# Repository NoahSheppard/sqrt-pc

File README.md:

## **UNDER CONSTRUCTION**

# Sqrt(PC)
A mini PC helper with a battery, and a microcontroller powerful enough to run programs itself...

For now this repo will be kept simple, with just the bare essentials in it. If you want a more in-depth guide into my inner thought process and how things came together over time, and feel that the commit history is weak, please find the Blueprint link [here](https://blueprint.hackclub.com/projects/13283)

# Bill Of Materials
<!-- BOM_START -->
| Reference | Qty | Value | Footprint | Price ($AUD unless marked) | Purchase-URL | Label | Notes |
| --- | --- | --- | --- | --- | --- | --- | --- |
| C46 | 1 | 100nF | C315C104K5R5TA:CAPRR254W54L381T254H466B | $0.70 | https://au.mouser.com/ProductDetail/KEMET/C315C104K5R5TA?qs=AHmto%252BvZ7OG2Mx7li%2Fn8YQ%3D%3D | Power Circuit - 100nF Capacitor |  |
| D1 | D2 | D3 | D5 | D6 | D7 | 6 | ~ | ScottoKeebs_Components:Diode_DO-35 | $- | N/A | Diodes for the Keyswitch array |  |
| D4 | 1 | LED_ARBG | LED_SMD:LED_Kingbright_AAA3528ESGCT | $0.74 | https://au.mouser.com/ProductDetail/Kingbright/AAA3528ESGCT?qs=HXFqYaX1Q2ztii0bK20PQg%3D%3D | LED for battery status |  |
| D9 | D10 | D11 | D12 | D13 | D14 | 6 | LED_SK6812MINI | ScottoKeebs_Components:LED_SK6812MINI | $- | N/A | RGB LEDs |  |
| DS1 | 1 | 4311 | 4311:MODULE_4311 | $9.37 | https://www.aliexpress.com/item/1005009447193931.html | Screen |  |
| J1 | 1 | Conn_01x02 | Connector_Molex:Molex_PicoBlade_53048-0210_1x02_P1.25mm_Horizontal | $3.76 | https://www.aliexpress.com/item/32807183020.html | Battery Connector | Can only get 50 min |
| Q1 | 1 | AO3401A | Package_TO_SOT_SMD:SOT-23W_Handsoldering | $0.97 | https://www.aliexpress.com/item/1005008934110148.html | Power Circuit - P-Channel MOSFET - Power Latch | Can only get 10 min |
| R2 | 1 | FMP100JR-52-2K2 | KiCADv6:FMP100JR_52_2K2 | $0.19 | https://au.mouser.com/ProductDetail/YAGEO/FMP100JR-52-2K2?qs=wcZjbqjoJegNfVYDP1qQwg%3D%3D | Power Circuit - 2.2kOhm Resistor |  |
| R3 | R4 | 2 | MFR-25FBF52-1K | MFR-25FBF52-1K:RESAD1100W55L680D260 | $0.31 | https://au.mouser.com/ProductDetail/YAGEO/MFR-25FTF52-1K47?qs=gt1LBUVyoHl4e3xmkemLyA%3D%3D | Power Circuit - 1.47 kOhms Resistor |  |
| R5 | R6 | 2 | RNC55H1002FMRE7 | RNC55H1002FMRE7:RESAD1081W64L635D269 | $0.85 | https://www.jaycar.com.au/10k-ohm-0-5-watt-metal-film-resistors-pack-of-8/p/RR0596?srsltid=AfmBOooZybZRjXbsL3loWYFdbOO8xv4_Spoyh16NfgIc8Q6pRosaol9- | Power Circuit - 10kOhm Resistor | Can only get in a 8 pack for this cheap |
| RN1 | 1 | CAY16-1003F4LF | CAY16-1003F4LF:RESCAF80P320X160X60-8N | $0.15 | https://au.mouser.com/ProductDetail/Bourns/CAY16-1003F4LF?qs=T7l%2FPuJnbcT4dvX5HXX74Q%3D%3D&srsltid=AfmBOoqqP7U5jdrc4c8albsdljesYeuMQMlg74Kuni7se9EsMJJ111ZA | Power Circuit - 4 100kOhm Resistors |  |
| S1 | S2 | S3 | S5 | S6 | S7 | 6 | ~ | Button_Switch_Keyboard:SW_Cherry_MX_1.00u_PCB | $- | N/A | Keyswitches | I own these already |
| S8 | 1 | PTS526_SMG15_SMTR2_LFS | PTS526_SMG15_SMTR2_LFS:SW_PTS526_SMG15_SMTR2_LFS | $0.24 | https://au.mouser.com/ProductDetail/CK/PTS526SMG15SMTR2-LFS?qs=Imq1NPwxi76tu1Vo5JUXUg%3D%3D | Power Button |  |
| U1 | 1 | WEMOSC3mini | RF_Module:WEMOS_C3_mini | $8.94 | https://www.aliexpress.com/item/1005004740051202.html | Microcontroller | Does not come with pin headers |
| U2 | 1 | TP4056-42-ESOP8 | Package_SO:SOIC-8-1EP_3.9x4.9mm_P1.27mm_EP2.41x3.3mm | $1.44 | https://www.lcsc.com/product-detail/C16581.html | Power Circuit - IC | Price in AUD | purchased in USD - rough conversion rate |
|  | 2 |  |  | $0.35 | https://core-electronics.com.au/header-male-pin-01x20.html | Microcontroller Pin Headers | Not in KiCad |
|  |  |  |  |  |  |  |  |
| Total Price | $28.01 |  |  |  |  |  |  |
|  |  |  |  |  |  |  |  |
<!-- BOM_END -->

# Schematic

# PCB

# CAD

# Firmware
tbd

## Disclaimer
AI was used in this project, to sanity check and to learn.

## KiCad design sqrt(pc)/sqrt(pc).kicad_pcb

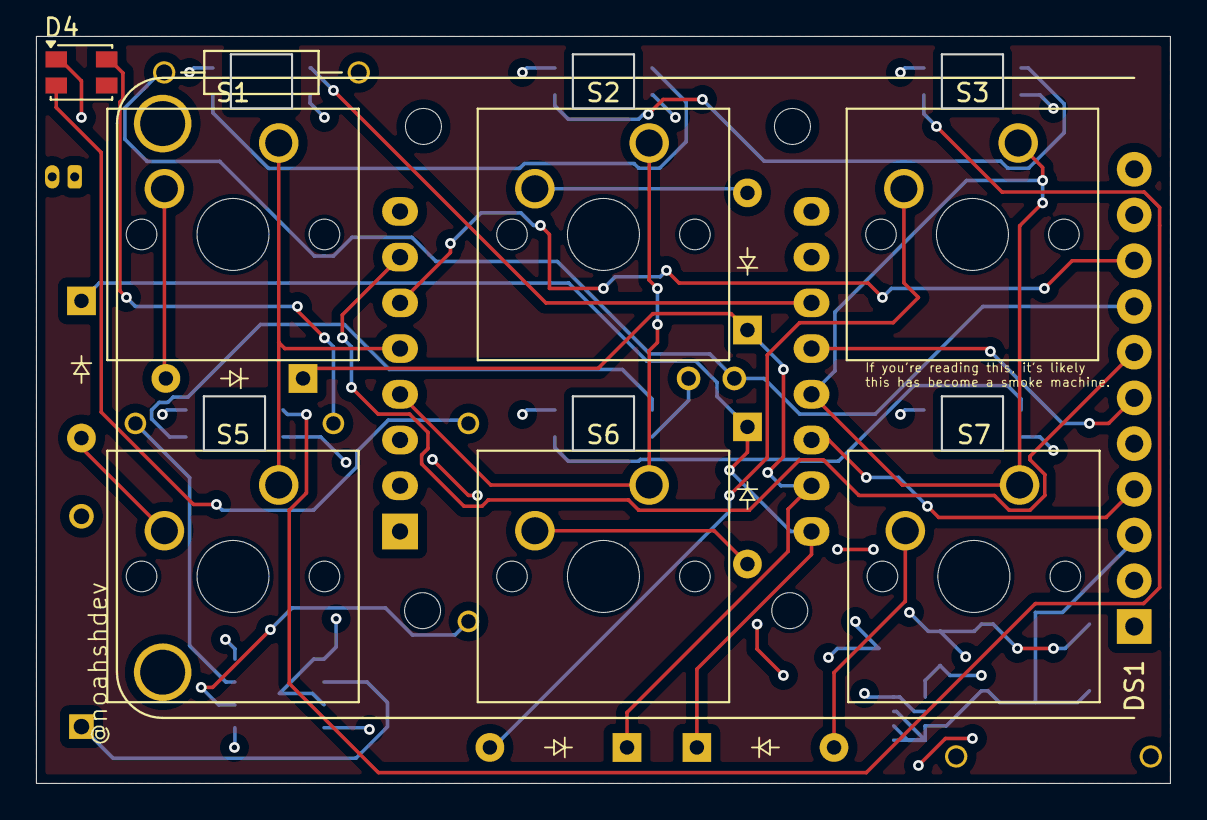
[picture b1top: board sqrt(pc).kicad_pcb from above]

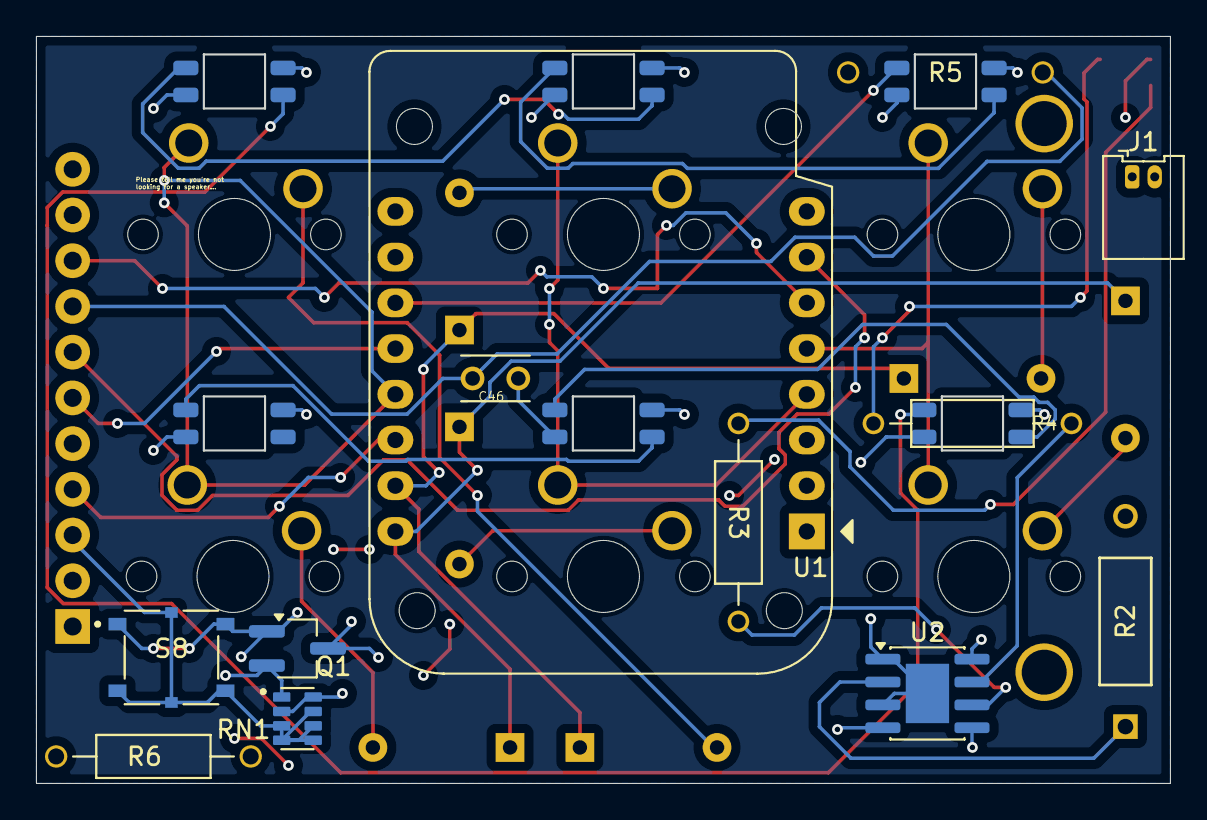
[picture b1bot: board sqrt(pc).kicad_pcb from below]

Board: 4 copper layers, 62.9 x 41.4 mm, 32 parts (17 on the bottom side), 33 nets.

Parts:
C46: 100nF; CAPRR254W54L381T254H466B
D1, D2, D3, D5, D6, D7: Diode_DO-35
D4: LED_ARBG; LED_Kingbright_AAA3528ESGCT
D9, D10, D11, D12, D13, D14: LED_SK6812MINI
DS1: 4311; MODULE_4311
J1: Conn_01x02; Molex_PicoBlade_53048-0210_1x02_P1.25mm_Horizontal
Q1: AO3401A; SOT-23W_Handsoldering
R2: FMP100JR-52-2K2; FMP100JR_52_2K2
R3, R4: MFR-25FBF52-1K; RESAD1100W55L680D260
R5, R6: RNC55H1002FMRE7; RESAD1081W64L635D269
RN1: CAY16-1003F4LF; RESCAF80P320X160X60-8N
S1, S2, S3, S5, S6, S7: SW_Cherry_MX_1.00u_PCB
S8: PTS526_SMG15_SMTR2_LFS; SW_PTS526_SMG15_SMTR2_LFS
U1: WEMOSC3mini; WEMOS_C3_mini
U2: TP4056-42-ESOP8; SOIC-8-1EP_3.9x4.9mm_P1.27mm_EP2.41x3.3mm

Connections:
3V3: D4.1 (A), D9.1 (VDD), D10.1 (VDD), D11.1 (VDD), D12.1 (VDD), D13.1 (VDD), D14.1 (VDD), DS1.1 (VIN), DS1.11 (BACKLIGHT), R5.1, U1.1 (EN), U1.8 (3V3), U2.8 (CE)
5V-VBus: Q1.3 (D), U1.9 (VBus), U2.4 (V_{CC})
BAT+: J1.1, Q1.2 (S), R6.1, RN1.1, U2.5 (BAT)
BAT_ADC: RN1.2, RN1.8, U1.3 (D2)
CS: DS1.7 (CS), U1.7 (D5)
Col 0: S1.1, S5.1, U1.5 (D0)
Col 1: S2.1, S6.1, U1.4 (D1)
Col 2: S3.1, S7.1, U1.13 (D8)
D/C: DS1.9 (D/C), U1.6 (D4)
GND: C46.2, D9.3 (VSS), D10.3 (VSS), D11.3 (VSS), D12.3 (VSS), D13.3 (VSS), D14.3 (VSS), DS1.3 (GND), J1.2, R2.2, RN1.3, RN1.4, RN1.5, RN1.6, RN1.7, S8.3, S8.4, S8.G1, S8.G2, U1.10 (GND), U2.1 (TEMP), U2.3 (GND), U2.9 (EPAD)
LED_DIN: D9.4 (DIN), U1.11 (D6)
unnamed: D1.2 (A), S1.2
unnamed: D2.2 (A), S2.2
unnamed: D3.2 (A), S3.2
unnamed: D4.4 (GK), R3.1
unnamed: D4.2 (RK), R4.1
unnamed: D5.2 (A), S5.2
unnamed: D6.2 (A), S6.2
unnamed: D7.2 (A), S7.2
unnamed: D9.2 (DOUT), D10.4 (DIN)
unnamed: D10.2 (DOUT), D11.4 (DIN)
unnamed: D11.2 (DOUT), D12.4 (DIN)
unnamed: D12.2 (DOUT), D13.4 (DIN)
unnamed: D13.2 (DOUT), D14.4 (DIN)
unnamed: C46.1, DS1.8 (~RST), R5.2
unnamed: R2.1, U2.2 (PROG)
unnamed: R4.2, U2.7 (~CHRG)
unnamed: R3.2, U2.6 (~STDBY)
Q1_GATE_HLD: Q1.1 (G), R6.2, S8.1, S8.2, U1.2 (D3)
Row 0: D1.1 (K), D2.1 (K), D3.1 (K), U1.15 (RX)
Row 1: D5.1 (K), D6.1 (K), D7.1 (K), U1.16 (TX)
SPI_CLK: DS1.4 (SCK), U1.14 (D10)
SPI_D: DS1.6 (MOSI), U1.12 (D7)

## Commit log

2026-03-07 init commit
2026-03-08 finished wiring PCB
2026-03-08 readme hehe :)
2026-03-23 BOM + a lot more I guess
2026-03-25 more images + bom
2026-03-25 try and fix bom reference in readme file
2026-03-25 script to hopeuflly embed bom in readme
2026-03-25 testing script
2026-03-25 chore: update BOM table from CSV
2026-03-25 updated images
